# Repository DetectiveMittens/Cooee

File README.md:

# Cooee (A LoRa Phone)                           
An open-source phone that can operate without GSM or LTE coverage. Utilising LoRa modulation and mesh networking to enable long range "off-grid" communication.

Come get involved or just chat here! -> [Discord](https://discord.gg/eWgrdjpTFj)

## Target Utilities/Functions
At time of writing (Jan 2026) Popular LoRa mesh networks only aim to support passing of text messages for public and private chat. Cooee aims to provide more of phone the features that consumers are used to

* __Voice calls:__ using 'Codec2' voice can be heavily compressed into small enough packets as to be supported by ~900MHz LoRa bandwidth limitations. Due to the delay that would happen if these packets needed to be retransmitted, calls would likely only be permitted between devices that have only 1 or 0 repeaters required between them.

* __Navigation:__ Using the data from OpenStreetMaps https://www.openstreetmap.org/ pre-loaded onto the device SD card a GPS reciever and infered location data based on signal strength to fixed repeaters of known location, the Cooee device should be able to locate itself well enough for navigation without ever needing a mobile data connection. 

* __Sending images and files:__
While LoRa bandwidth will likely never support sending large files (videos etc) piecemeal file transfers of compressed images (jpgs) should be possible

## Applications / Uses: 
The Cooee should ideally contribute to solving the following problems
  * Distress calls for help in remote locations
  * Basic communication in areas without GSM/LTE infrastructure
  * Dissemination of natural disaster and emergency warnings
  * Marking/Logging GPS locations. Users could tag and share hazards such as landmines (UXO/ERW), fires, vehicle collisions, chemical spills or dangerous wildlife.
  * Navigation in areas without GSM/LTE infrastructure

## Philosophy: 
My dream for this device is that is could demonstrate my ideals for what the future of harware aught to look like. This means deliberately achieving aims in ways which are not the 'best practice', such as;
 * Keeping code simple, using the Arduino framework isntead of ESP-IDF. The idea being that this increases how many people around the world would be able to understand and modify the device firmware, helping ensure that it is kept on track with providing maximum utility to the lives of those people who own one.
 * No electronic components smaller than 805 (no micro-soldering), this allows people to hand solder in repairs and hand assembly the PCB's with minimal equipement
 * SMT components on one side of the PCB only. Again allowing for easy assembly and repair without specialized gear
 * Plastic parts moulded from post consumer waste. Many plastics today claim to be 'recycled' when really they are just 'factory seconds', they have never used and discarded. I would like the plastic components of the Cooee to be injection moulded from recycld post consumer PET bottled pulled from waterways. Many countries in SEA are flooded with drink bottles made of PET. an easily recycled thermoplastic.
 * Hardware ownership. Increasingly, modern mobile devices are not really the property of the customer who paid hundreds, sometimes thousands of dollars to 'own' it. They are not free to modify it or install custom firmware, even creating custom firmware is a task far beyond the capabilities of most. This leaves people at the mercy of whatever bloatware the manufacturers have bundled. This bundled software often; listens to you at all times, sends transcripts of your conversations to corporate servers, advertises products at you, insists on volunteering additional personal details to enable use ect. I think it's high time that the cleverst people in the world put thier efforts towards creating machines that provide all of the utility that benefits us without any of the data harvesting and advertising. Imagine how nice it would be to use a navigator which simply puts your GPS position on a locally loaded map, it doesn't start suffocating your device by chewing up huge amounts of bandwidth or report everywhere you go to a server or try to encourage spending on nearby businesses. Imagine a navigator which just helps you nagivate in the most lightweight and unobtrusive way possible.
 This is the philisophy I want to see applied to all the functions of the Cooee software.

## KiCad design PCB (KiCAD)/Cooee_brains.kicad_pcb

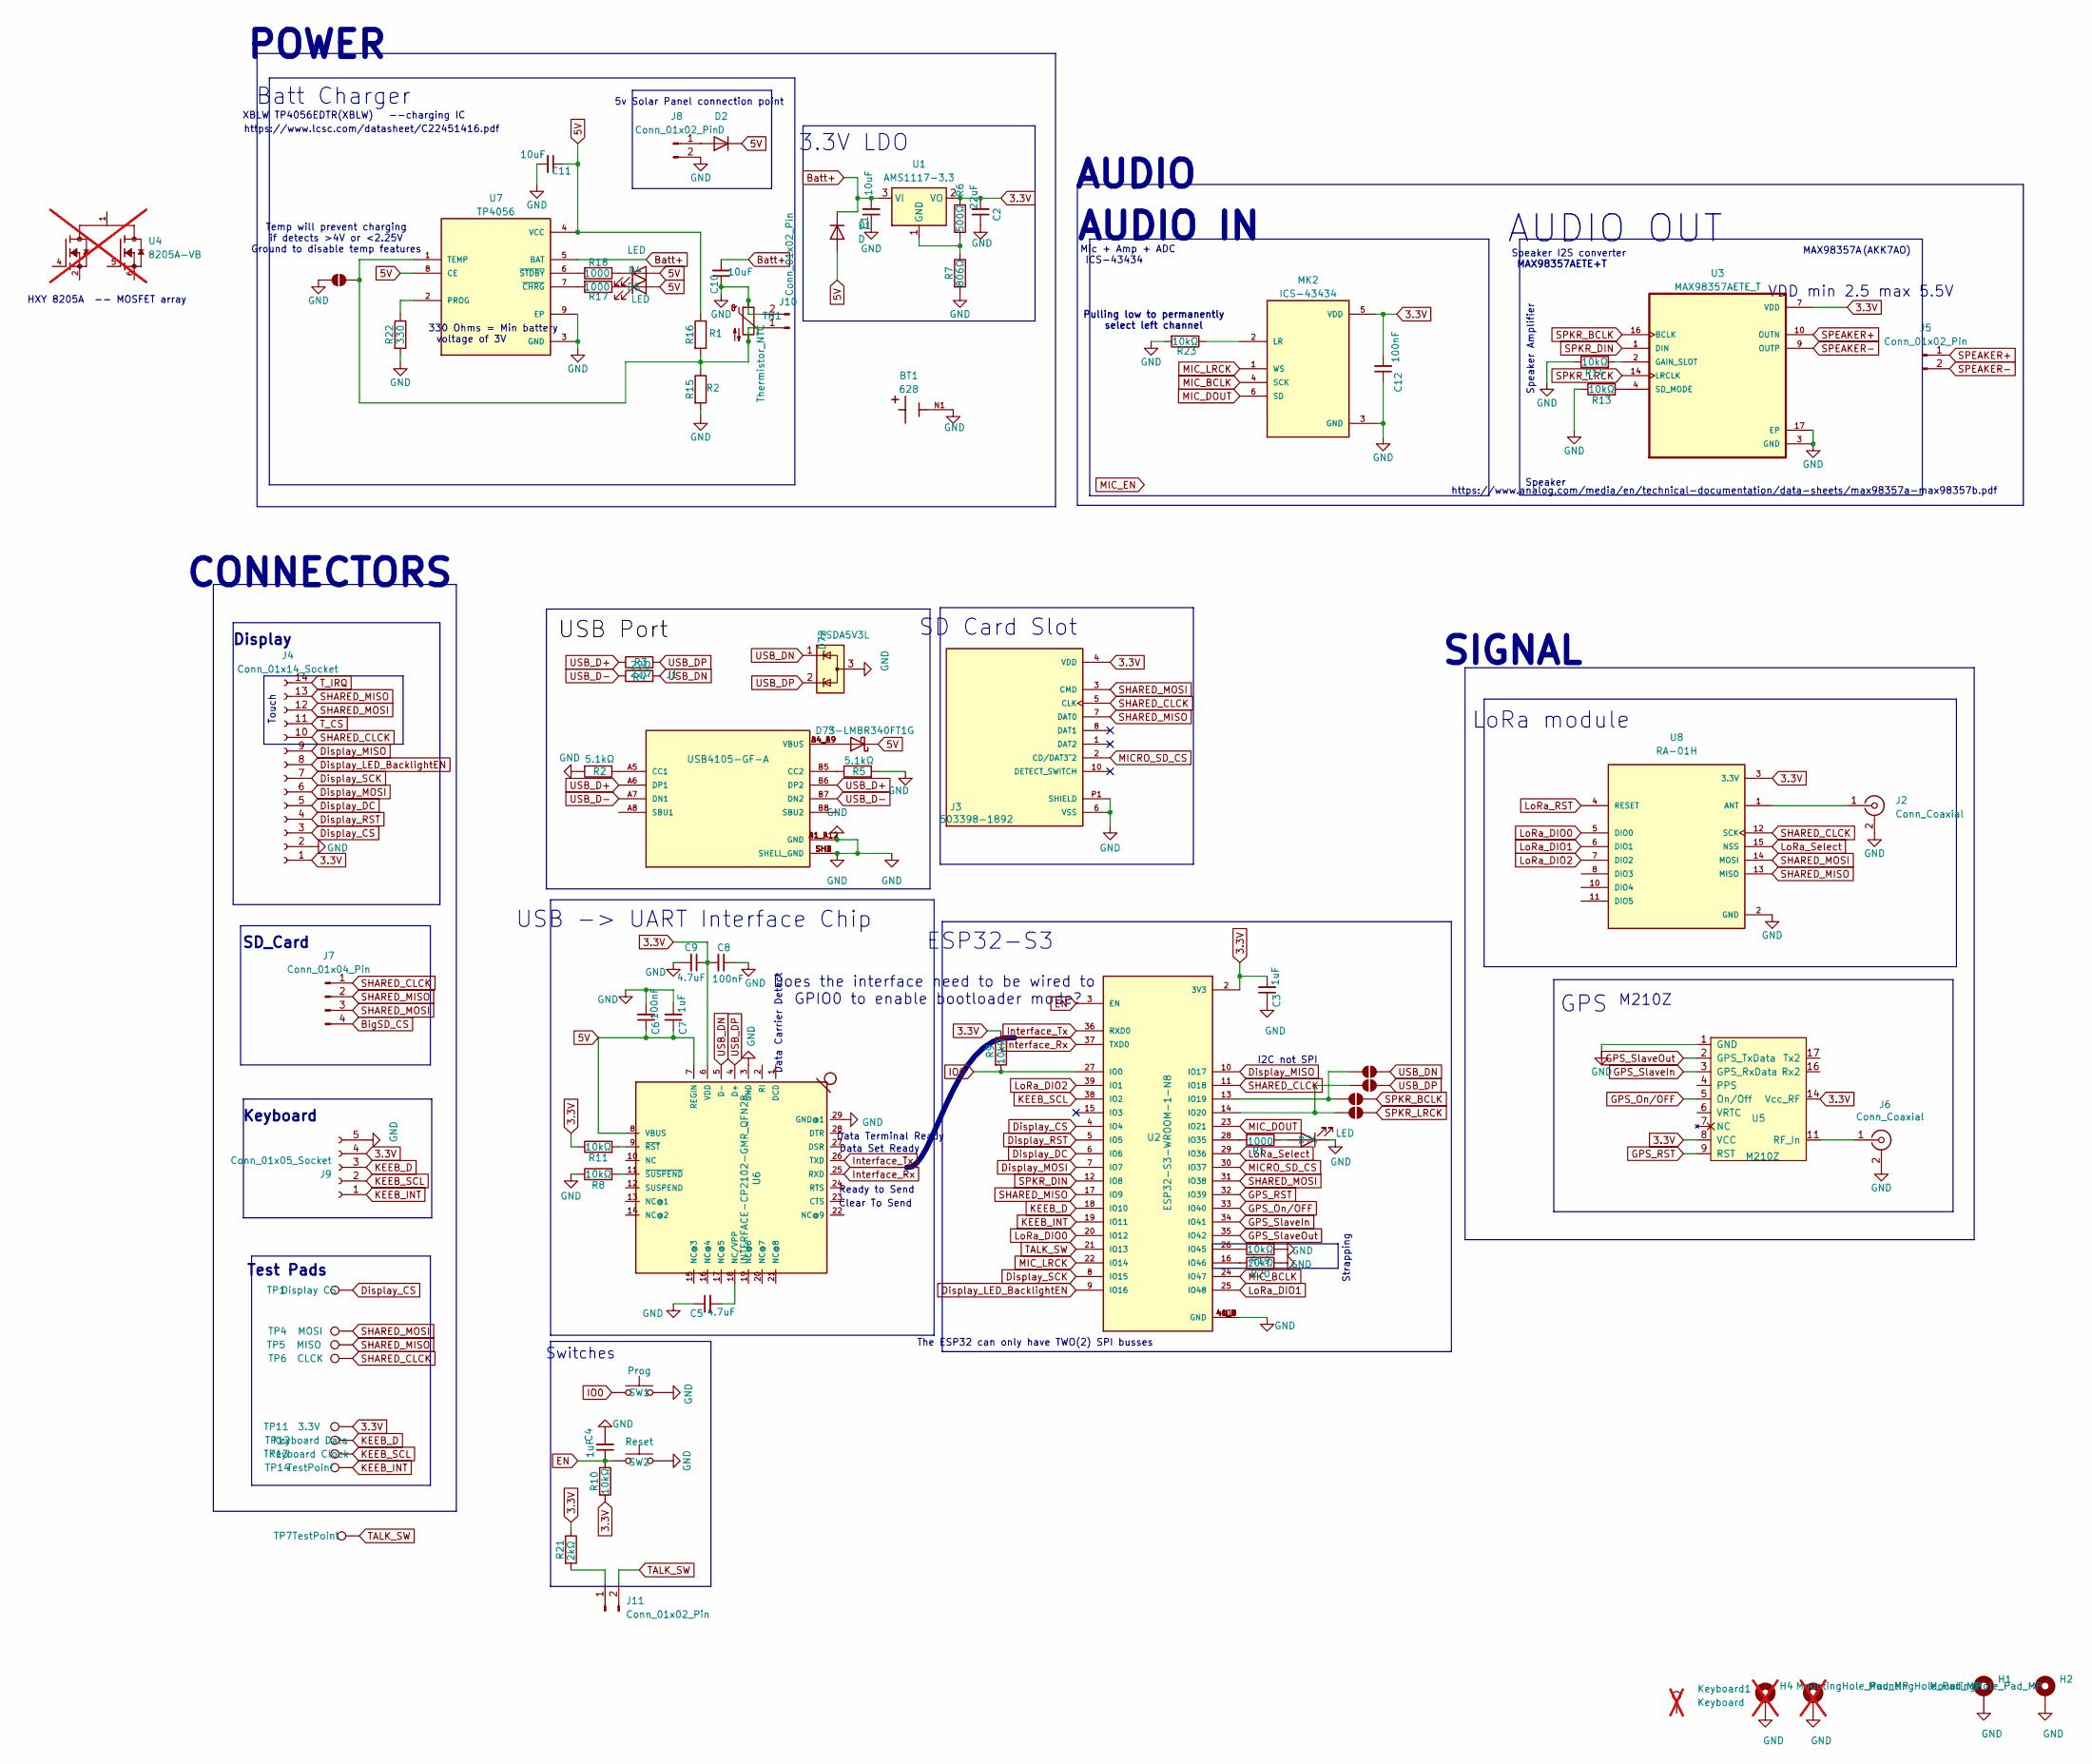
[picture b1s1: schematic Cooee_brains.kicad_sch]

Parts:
BT1: 628; BAT_628; PARTREV A; DigiKey_Part_Number 36-628-ND
C1, C10, C11: 10uF; C_0805_2012Metric
C2: 22uF; C_0805_2012Metric
C3, C7: 1uF; C_0805_2012Metric
C4: 1uF; C_0805_2012Metric_Pad1.18x1.45mm_HandSolder
C5, C9: 4.7uF; C_0805_2012Metric
C6, C8, C12: 100nF; C_0805_2012Metric
D1, D2: D; D_0805_2012Metric_Pad1.15x1.40mm_HandSolder
D4, D5, D74: LED; C_0805_2012Metric
D72: ESDA5V3L; SOT-23_Handsoldering
D73: S-LMBR340FT1G; D_SOD-123FL
H1, H2: MountingHole_Pad_MP; MountingHole_3.2mm_M3_DIN965_Pad_TopBottom
H3, H4: MountingHole_Pad_MP; MountingHole_3.2mm_M3_DIN965_Pad_TopBottom; not fitted
J1: USB4105-GF-A; USB_C_Receptacle_GCT_USB4105-xx-A_16P_TopMnt_Horizontal
J2, J6: Conn_Coaxial; U.FL_Molex_MCRF_73412-0110_Vertical
J3: 503398-1892; MOLEX_503398-1892; PARTREV 0
J4: Conn_01x14_Socket; PinSocket_1x14_P2.54mm_Horizontal
J5, J8, J10, J11: Conn_01x02_Pin; PinHeader_1x02_P2.54mm_Horizontal
J7: Conn_01x04_Pin; PinHeader_1x04_P2.54mm_Horizontal
J9: Conn_01x05_Socket; PinSocket_1x05_P2.54mm_Horizontal
JP1, JP2, JP3, JP4, JP5: SolderJumper_2_Open; SolderJumper-2_P1.3mm_Open_RoundedPad1.0x1.5mm
Keyboard1: Keyboard; TestPoint_Pad_1.0x1.0mm; not fitted
MK2: ICS-43434; MIC_ICS-43434
R1, R17, R18: 1000; C_0805_2012Metric_Pad1.18x1.45mm_HandSolder
R2, R5: 5.1kΩ; R_0805_2012Metric
R3, R4: 22Ω; R_0805_2012Metric
R6: 500Ω; C_0805_2012Metric_Pad1.18x1.45mm_HandSolder
R7: 806Ω; C_0805_2012Metric_Pad1.18x1.45mm_HandSolder
R8, R9, R10, R11, R13, R14, R19, R20, R23: 10kΩ; C_0805_2012Metric_Pad1.18x1.45mm_HandSolder
R15: R2; C_0805_2012Metric_Pad1.18x1.45mm_HandSolder
R16: R1; C_0805_2012Metric_Pad1.18x1.45mm_HandSolder
R21: 2kΩ; C_0805_2012Metric_Pad1.18x1.45mm_HandSolder
R22: 330; C_0805_2012Metric_Pad1.18x1.45mm_HandSolder
SW1: Prog; SW_SPST_B3U-1000P_MovedText
SW2: Reset; SW_SPST_B3U-1000P_MovedText
TH1: Thermistor_NTC; R_0805_2012Metric_Pad1.20x1.40mm_HandSolder
TP1: Display CS; TestPoint_Pad_1.0x1.0mm
TP4: MOSI; TestPoint_Pad_1.0x1.0mm
TP5: MISO; TestPoint_Pad_1.0x1.0mm
TP6: CLCK; TestPoint_Pad_1.0x1.0mm
TP7, TP14: TestPoint; TestPoint_Pad_1.0x1.0mm
TP11: 3.3V; TestPoint_Pad_1.0x1.0mm
TP12: Keyboard Data; TestPoint_Pad_1.0x1.0mm
TP13: Keyboard Clock; TestPoint_Pad_1.0x1.0mm
U1: AMS1117-3.3; SOT-223-3_TabPin2
U2: ESP32-S3-WROOM-1-N8; ESP32-S3-WROOM-1
U3: MAX98357AETE_T; TQFN-16-1EP_3x3mm_P0.5mm_EP1.6x1.6mm
U4: 8205A-VB; SOP65P640X120-8N; PARTREV NA; not fitted
U5: M210Z
U6: INTERFACE-CP2102-GMR_QFN28_; QFN28G_0.5-5X5MM; MPN CP2102-GMR
U7: TP4056; SOP127P600X175-9N
U8: RA-01H; Ai-Thinker-Ra-01-LoRa; PARTREV V1.0; DigiKey_Part_Number 4570-RA-01HCT-ND

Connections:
3.3V: C2.2, C3.2, C8.2, C9.1, C12.2, J3.4 (VDD), J4.1, J9.4, MK2.5 (VDD), R6.2, R9.1, R10.2, R11.1, R21.1, TP11.1, U1.2 (VO), U2.2 (3V3), U3.7 (VDD), U3.8 (VDD), U5.8 (VCC), U5.14 (Vcc_RF), U6.6 (VDD), U8.3 (3.3V)
5V: C6.1, C7.1, C11.1, D1.2 (A), D2.1 (K), D4.2 (A), D5.2 (A), D73.1 (K), R16.1, U6.7 (REGIN), U6.8 (VBUS), U7.4 (VCC), U7.8 (CE)
Batt+: C1.2, C10.2, D1.1 (K), U1.3 (VI), U7.5 (BAT)
BigSD_CS: J7.4
Display_CS: J4.3, TP1.1, U2.4 (IO4)
Display_DC: J4.5, U2.6 (IO6)
Display_LED_BacklightEN: J4.8, U2.9 (IO16)
Display_MISO: J4.9, U2.10 (IO17)
Display_MOSI: J4.6, U2.7 (IO7)
Display_RST: J4.4, U2.5 (IO5)
Display_SCK: J4.7, U2.8 (IO15)
EN: C4.1, R10.1, SW2.1, U2.3 (EN)
GND: BT1.N1, BT1.N2, BT1.N3, C1.1, C2.1, C3.1, C4.2, C5.1, C6.2, C7.2, C8.1, C9.2, C10.1, C11.2, C12.1, D72.3 (A), D74.1 (K), H1.1, H1.MP, H2.1, H2.MP, H3.MP, H4.MP, J1.A1_B12 (GND), J1.B1_A12 (GND), J1.S1, J1.SH1 (SHELL_GND), J1.SH2 (SHELL_GND), J1.SH3 (SHELL_GND), J1.SH4 (SHELL_GND), J2.2 (Ext), J3.6 (VSS), J3.9 (VSS), J3.P1 (SHIELD), J3.P2 (SHIELD), J3.P3 (SHIELD), J3.P4 (SHIELD), J4.2, J6.2 (Ext), J8.2, J9.5, J10.2, JP5.1 (A), MK2.3 (GND), R2.2, R5.2, R7.2, R8.1, R13.1, R14.1, R15.2, R19.2, R20.2, R22.2, R23.2, SW1.2, SW2.2, TH1.1, U2.1 (GND), U2.40 (GND), U2.41, U2.41_1 (GND), U2.41_2 (GND), U2.41_3 (GND), U2.41_4 (GND), U2.41_5 (GND), U2.41_6 (GND), U2.41_7 (GND), U2.41_8 (GND), U2.41_9 (GND), U2.GND, U3.3 (GND), U3.11 (GND), U3.15 (GND), U3.17 (EP), U5.1 (GND), U6.3 (GND), U6.29 (GND@1), U7.3 (GND), U7.9 (EP), U8.2 (GND), U8.9 (GND), U8.16 (GND)
GPS_On/OFF: U2.33 (IO40), U5.5 (On/Off)
GPS_RST: U2.32 (IO39), U5.9 (RST)
GPS_SlaveIn: U2.34 (IO41), U5.3 (GPS_RxData)
GPS_SlaveOut: U2.35 (IO42), U5.2 (GPS_TxData)
IO0: R9.2, SW1.1, U2.27 (IO0)
Interface_Rx: U2.37 (TXD0), U6.25 (RXD)
Interface_Tx: U2.36 (RXD0), U6.26 (TXD)
KEEB_D: J9.3, TP12.1, U2.18 (IO10)
KEEB_INT: J9.1, TP14.1, U2.19 (IO11)
KEEB_SCL: J9.2, TP13.1, U2.38 (IO2)
LoRa_DIO0: U2.20 (IO12), U8.5 (DIO0)
LoRa_DIO1: U2.25 (IO48), U8.6 (DIO1)
LoRa_DIO2: U2.39 (IO1), U8.7 (DIO2)
LoRa_RST: U8.4 (RESET)
LoRa_Select: U2.29 (IO36), U8.15 (NSS)
MICRO_SD_CS: J3.2 (CD/DAT3^2), U2.30 (IO37)
MIC_BCLK: MK2.4 (SCK), U2.24 (IO47)
MIC_DOUT: MK2.6 (SD), U2.23 (IO21)
MIC_LRCK: MK2.1 (WS), U2.22 (IO14)
unnamed: D2.2 (A), J8.1
unnamed: D4.1 (K), R18.1
unnamed: D5.1 (K), R17.1
unnamed: D73.2 (A), J1.A4_B9 (VBUS), J1.B4_A9 (VBUS)
unnamed: D74.2 (A), R1.1
unnamed: J1.A5 (CC1), R2.1
unnamed: J1.B5 (CC2), R5.1
unnamed: J2.1 (In), U8.1 (ANT)
unnamed: J6.1 (In), U5.11 (RF_In)
unnamed: J10.1, JP5.2 (B), R15.1, R16.2, TH1.2, U7.1 (TEMP)
unnamed: J11.1, R21.2
unnamed: JP1.1 (A), JP3.1 (A), U2.13 (IO19)
unnamed: JP2.1 (A), JP4.1 (A), U2.14 (IO20)
unnamed: MK2.2 (LR), R23.1
unnamed: R6.1, R7.1, U1.1 (GND)
unnamed: R1.2, U2.28 (IO35)
unnamed: R19.1, U2.26 (IO45)
unnamed: R20.1, U2.16 (IO46)
unnamed: R14.2, U3.2 (GAIN_SLOT)
unnamed: R13.2, U3.4 (SD_MODE)
unnamed: U4.1, U4.8
unnamed: U4.2, U4.3
unnamed: U4.6, U4.7
unnamed: C5.2, U6.18 (NC/VPP)
unnamed: R11.2, U6.9 (~RST)
unnamed: R8.2, U6.11 (~SUSPEND)
unnamed: R22.1, U7.2 (PROG)
unnamed: R17.2, U7.7 (~CHRG)
unnamed: R18.2, U7.6 (~STDBY)
SHARED_CLCK: J3.5 (CLK), J4.10, J7.1, TP6.1, U2.11 (IO18), U8.12 (SCK)
SHARED_MISO: J3.7 (DAT0), J4.13, J7.2, TP5.1, U2.17 (IO9), U8.13 (MISO)
SHARED_MOSI: J3.3 (CMD), J4.12, J7.3, TP4.1, U2.31 (IO38), U8.14 (MOSI)
SPEAKER+: J5.1, U3.10 (OUTN)
SPEAKER-: J5.2, U3.9 (OUTP)
SPKR_BCLK: JP3.2 (B), U3.16 (BCLK)
SPKR_DIN: U2.12 (IO8), U3.1 (DIN)
SPKR_LRCK: JP4.2 (B), U3.14 (LRCLK)
TALK_SW: J11.2, TP7.1, U2.21 (IO13)
T_CS: J4.11
T_IRQ: J4.14
USB_D+: J1.A6 (DP1), J1.B6 (DP2), R3.1
USB_D-: J1.A7 (DN1), J1.B7 (DN2), R4.1
USB_DN: D72.1 (K), JP1.2 (B), R4.2, U6.5 (D-)
USB_DP: D72.2 (K), JP2.2 (B), R3.2, U6.4 (D+)

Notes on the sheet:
SIGNAL
Does the interface need to be wired to GPIO0 to enable bootloader mode?
Data Set Ready
MAX98357AETE+T
Data Carrier Detect
AUDIO
The ESP32 can only have TWO(2) SPI busses
https://www.analog.com/media/en/technical-documentation/data-sheets/max98357a-max98357b.pdf
POWER
Speaker Amplifier
M210Z
https://www.lcsc.com/datasheet/C22451416.pdf
voltage of 3V
XBLW TP4056EDTR(XBLW) --charging IC
Strapping
AUDIO IN
Speaker I2S converter
ESP32-S3
Switches
ICS-43434
HXY 8205A -- MOSFET array
SD Card Slot
Ready to Send
Speaker
VDD min 2.5 max 5.5V
Clear To Send
I2C not SPI
SD_Card
5v Solar Panel connection point
AUDIO OUT
Batt Charger
CONNECTORS
Temp will prevent charging if detects >4V or <2.25V Ground to disable temp features
Pulling low to permanently select left channel
USB -> UART Interface Chip
Keyboard
3.3V LDO
Touch
GPS
Test Pads

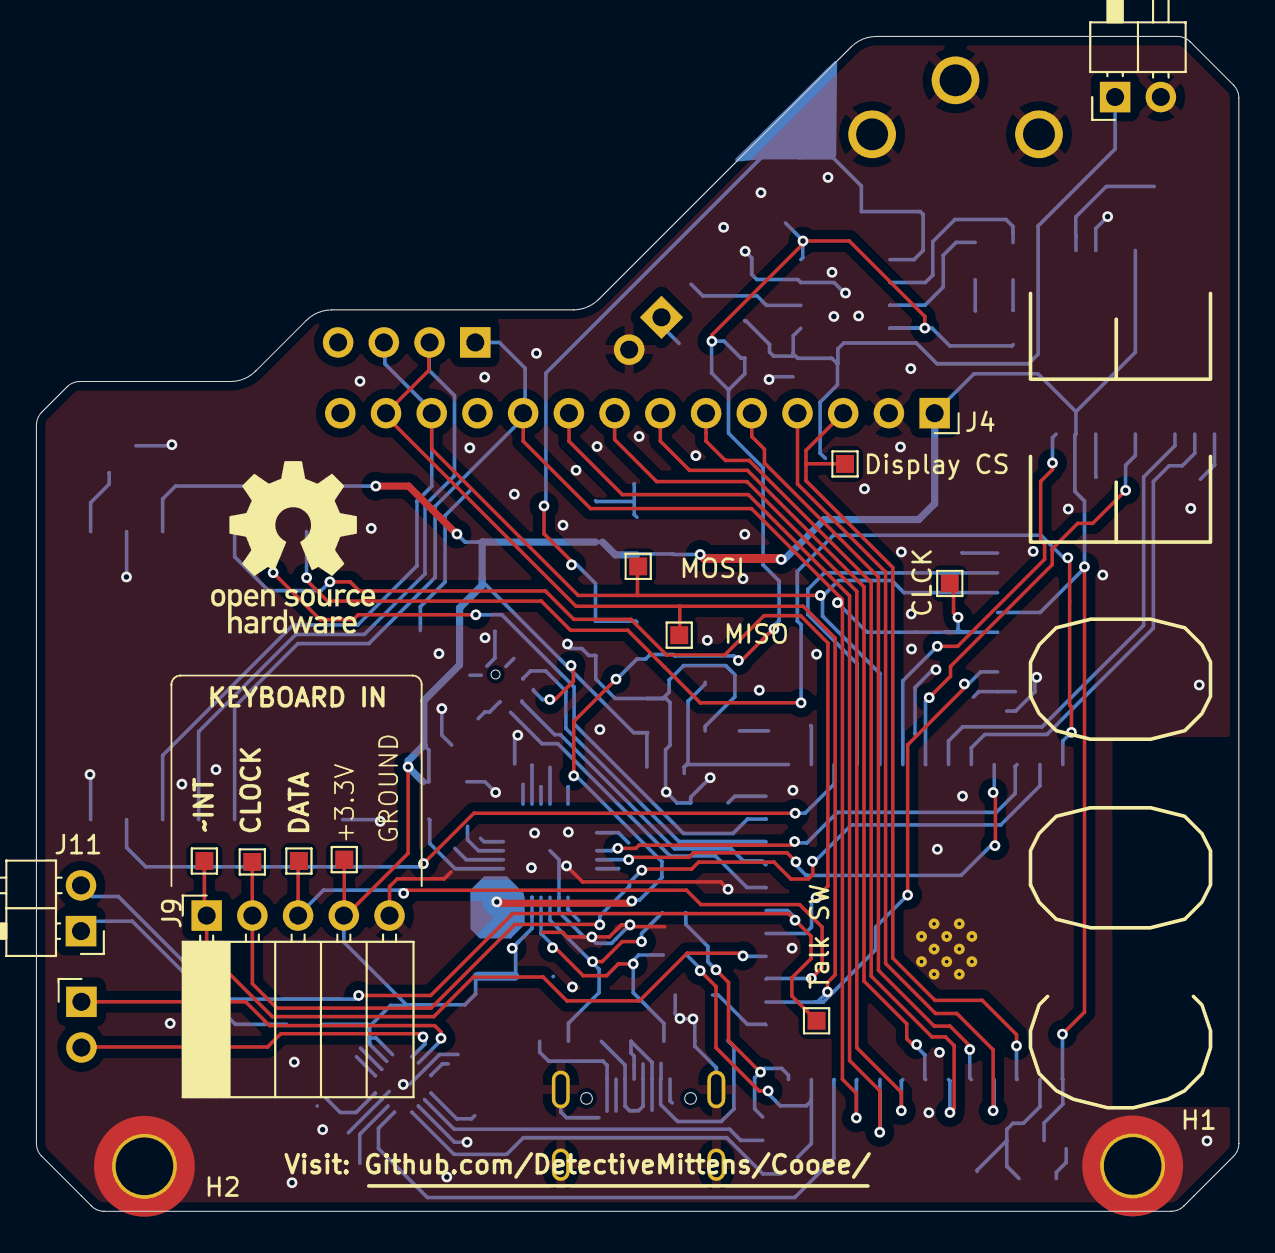
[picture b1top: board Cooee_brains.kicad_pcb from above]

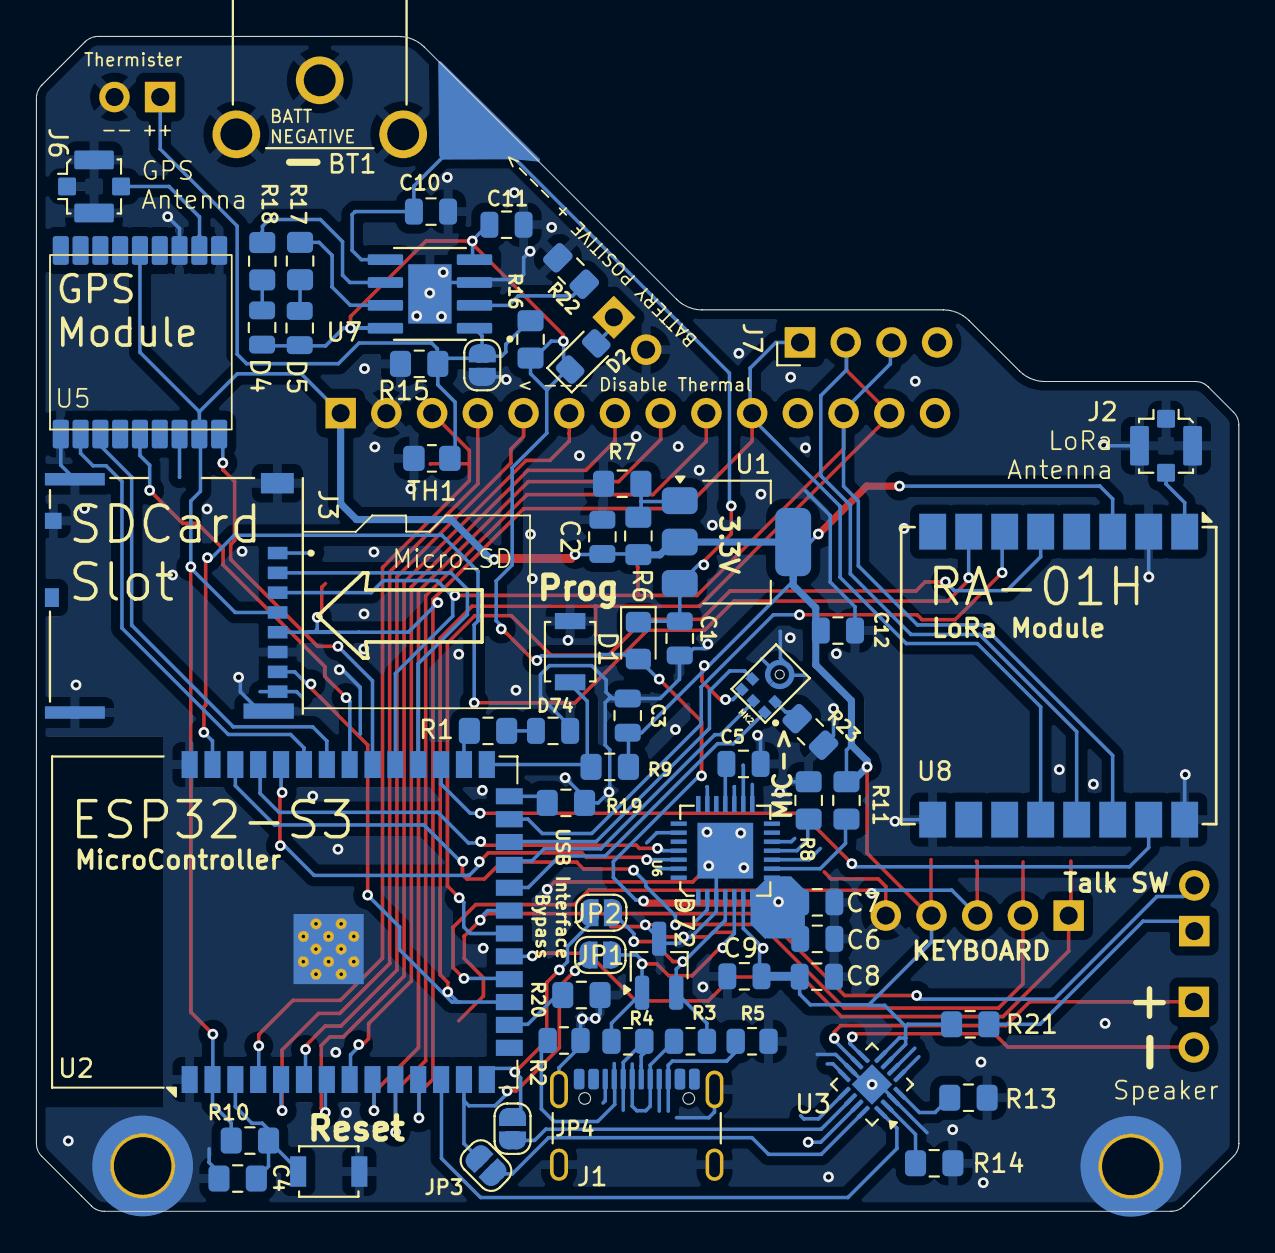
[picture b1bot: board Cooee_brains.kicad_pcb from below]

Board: 2 copper layers, 66.8 x 65.3 mm, 79 parts (63 on the bottom side), 68 nets.

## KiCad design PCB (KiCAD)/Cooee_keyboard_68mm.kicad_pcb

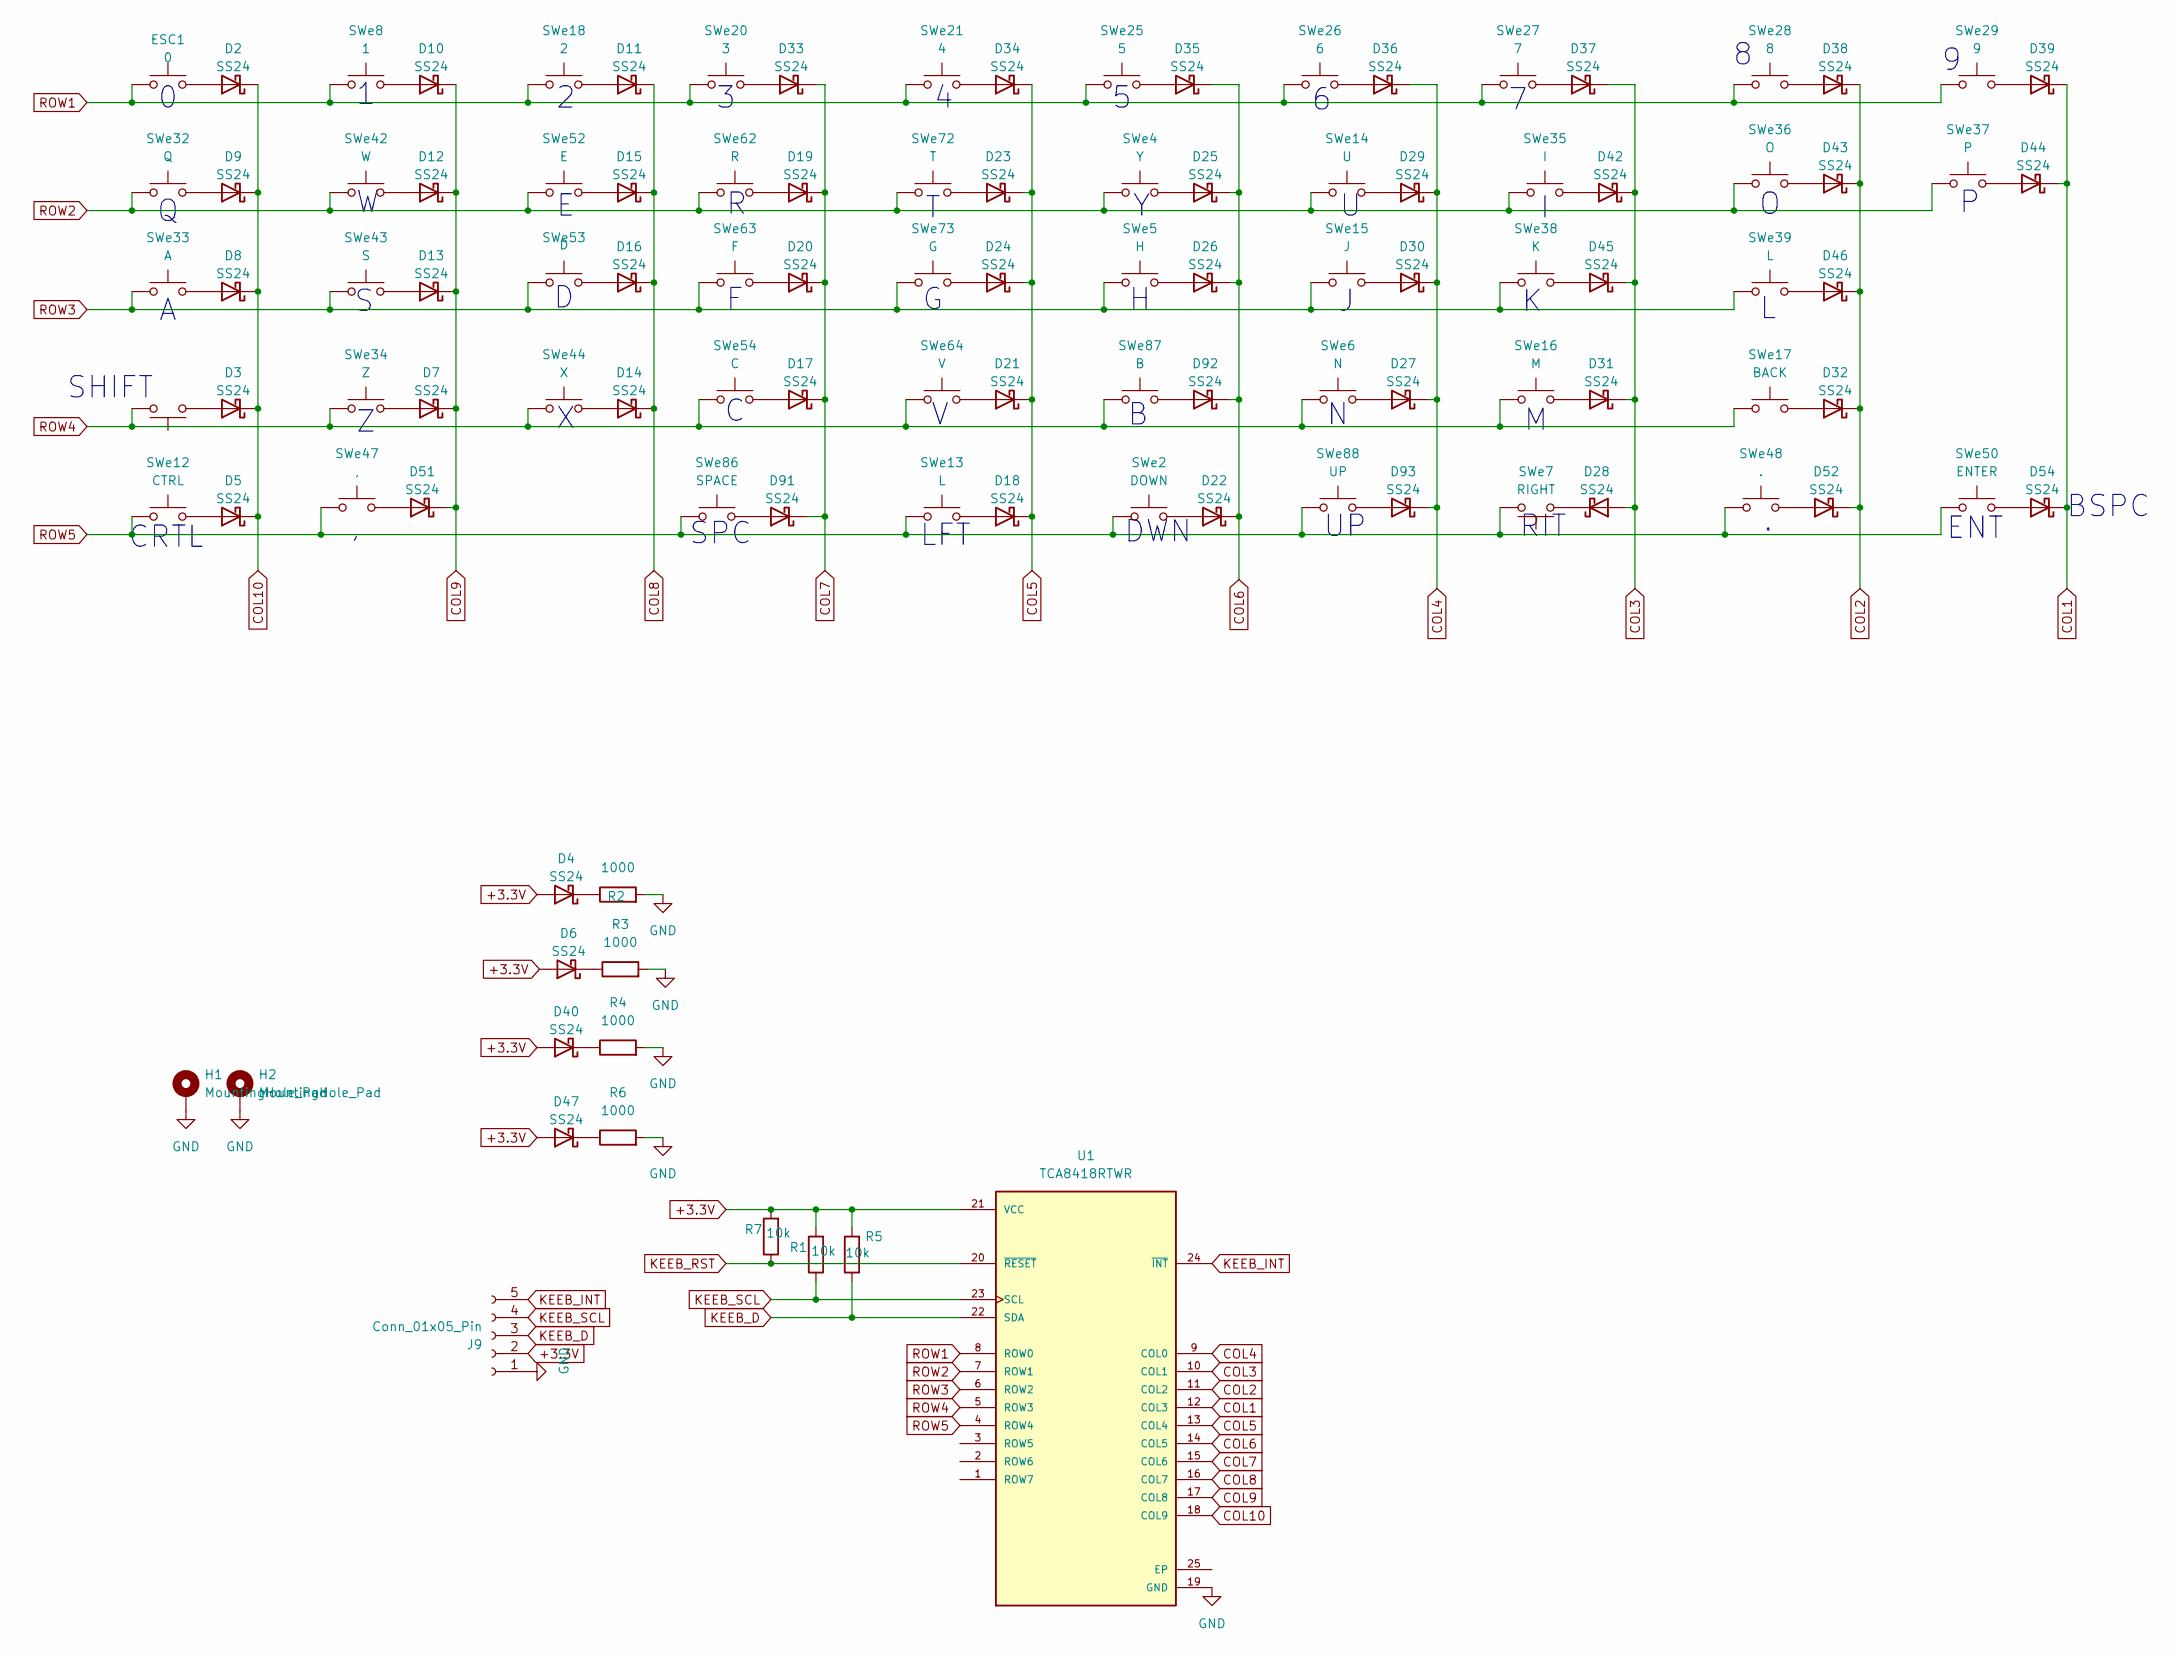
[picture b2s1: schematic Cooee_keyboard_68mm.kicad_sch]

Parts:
D2, D3, D4, D5, D6, D7, D8, D9, D10, D11, D12, D13, D14, D15, D16, D17, D18, D19, D20, D21, D22, D23, D24, D25, D26, D27, D28, D29, D30, D31, D32, D33, D34, D35, D36, D37, D38, D39, D40, D42, D43, D44, D45, D46, D47, D51, D52, D54, D91, D92, D93: SS24; D_0805_2012Metric
ESC1: 0; SW_SPST_B3U-1000P_MovedText
H1, H2: MountingHole_Pad; MountingHole_3.2mm_M3_DIN965_Pad_TopBottom
J9: Conn_01x05_Pin; PinHeader_1x05_P2.54mm_Horizontal
R1, R5, R7: 10k; R_0805_2012Metric_Pad1.20x1.40mm_HandSolder
R2, R3, R4, R6: 1000; R_0805_2012Metric_Pad1.20x1.40mm_HandSolder
SWe2: DOWN; SW_SPST_B3U-1000P_MovedText
SWe4: Y; SW_SPST_B3U-1000P_MovedText
SWe5: H; SW_SPST_B3U-1000P_MovedText
SWe6: N; SW_SPST_B3U-1000P_MovedText
SWe7: RIGHT; SW_SPST_B3U-1000P_MovedText
SWe8: 1; SW_SPST_B3U-1000P_MovedText
SWe12: CTRL; SW_SPST_B3U-1000P_MovedText
SWe13, SWe39: L; SW_SPST_B3U-1000P_MovedText
SWe14: U; SW_SPST_B3U-1000P_MovedText
SWe15: J; SW_SPST_B3U-1000P_MovedText
SWe16: M; SW_SPST_B3U-1000P_MovedText
SWe17: BACK; SW_SPST_B3U-1000P_MovedText
SWe18: 2; SW_SPST_B3U-1000P_MovedText
SWe20: 3; SW_SPST_B3U-1000P_MovedText
SWe21: 4; SW_SPST_B3U-1000P_MovedText
SWe24: SFT; SW_SPST_B3U-1000P_MovedText
SWe25: 5; SW_SPST_B3U-1000P_MovedText
SWe26: 6; SW_SPST_B3U-1000P_MovedText
SWe27: 7; SW_SPST_B3U-1000P_MovedText
SWe28: 8; SW_SPST_B3U-1000P_MovedText
SWe29: 9; SW_SPST_B3U-1000P_MovedText
SWe32: Q; SW_SPST_B3U-1000P_MovedText
SWe33: A; SW_SPST_B3U-1000P_MovedText
SWe34: Z; SW_SPST_B3U-1000P_MovedText
SWe35: I; SW_SPST_B3U-1000P_MovedText
SWe36: O; SW_SPST_B3U-1000P_MovedText
SWe37: P; SW_SPST_B3U-1000P_MovedText
SWe38: K; SW_SPST_B3U-1000P_MovedText
SWe42: W; SW_SPST_B3U-1000P_MovedText
SWe43: S; SW_SPST_B3U-1000P_MovedText
SWe44: X; SW_SPST_B3U-1000P_MovedText
SWe47: ,; SW_SPST_B3U-1000P_MovedText
SWe48: .; SW_SPST_B3U-1000P_MovedText
SWe50: ENTER; SW_SPST_B3U-1000P_MovedText
SWe52: E; SW_SPST_B3U-1000P_MovedText
SWe53: D; SW_SPST_B3U-1000P_MovedText
SWe54: C; SW_SPST_B3U-1000P_MovedText
SWe62: R; SW_SPST_B3U-1000P_MovedText
SWe63: F; SW_SPST_B3U-1000P_MovedText
SWe64: V; SW_SPST_B3U-1000P_MovedText
SWe72: T; SW_SPST_B3U-1000P_MovedText
SWe73: G; SW_SPST_B3U-1000P_MovedText
SWe86: SPACE; SW_SPST_B3U-1000P_MovedText
SWe87: B; SW_SPST_B3U-1000P_MovedText
SWe88: UP; SW_SPST_B3U-1000P_MovedText
U1: TCA8418RTWR; QFN50P400X400X100-25N; PARTREV G

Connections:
+3.3V: D4.2 (A), D6.2 (A), D40.2 (A), D47.2 (A), J9.2, R1.2, R5.2, R7.2, U1.21 (VCC)
COL1: D39.1 (K), D44.1 (K), D54.1 (K), U1.12 (COL3)
COL2: D32.1 (K), D38.1 (K), D43.1 (K), D46.1 (K), D52.1 (K), U1.11 (COL2)
COL3: D28.2 (A), D31.1 (K), D37.1 (K), D42.1 (K), D45.1 (K), U1.10 (COL1)
COL4: D27.1 (K), D29.1 (K), D30.1 (K), D36.1 (K), D93.1 (K), U1.9 (COL0)
COL5: D18.1 (K), D21.1 (K), D23.1 (K), D24.1 (K), D34.1 (K), U1.13 (COL4)
COL6: D22.1 (K), D25.1 (K), D26.1 (K), D35.1 (K), D92.1 (K), U1.14 (COL5)
COL7: D17.1 (K), D19.1 (K), D20.1 (K), D33.1 (K), D91.1 (K), U1.15 (COL6)
COL8: D11.1 (K), D14.1 (K), D15.1 (K), D16.1 (K), U1.16 (COL7)
COL9: D7.1 (K), D10.1 (K), D12.1 (K), D13.1 (K), D51.1 (K), U1.17 (COL8)
COL10: D2.1 (K), D3.1 (K), D5.1 (K), D8.1 (K), D9.1 (K), U1.18 (COL9)
GND: H1.1, H2.1, J9.1, R2.2, R3.2, R4.2, R6.2, U1.19 (GND)
KEEB_D: J9.3, R5.1, U1.22 (SDA)
KEEB_INT: J9.5, U1.24 (~INT)
KEEB_RST: R7.1, U1.20 (~RESET)
KEEB_SCL: J9.4, R1.1, U1.23 (SCL)
unnamed: D2.2 (A), ESC1.2
unnamed: D3.2 (A), SWe24.2
unnamed: D4.1 (K), R2.1
unnamed: D5.2 (A), SWe12.2
unnamed: D6.1 (K), R3.1
unnamed: D7.2 (A), SWe34.2
unnamed: D8.2 (A), SWe33.2
unnamed: D9.2 (A), SWe32.2
unnamed: D10.2 (A), SWe8.2
unnamed: D11.2 (A), SWe18.2
unnamed: D12.2 (A), SWe42.2
unnamed: D13.2 (A), SWe43.2
unnamed: D14.2 (A), SWe44.2
unnamed: D15.2 (A), SWe52.2
unnamed: D16.2 (A), SWe53.2
unnamed: D17.2 (A), SWe54.2
unnamed: D18.2 (A), SWe13.2
unnamed: D19.2 (A), SWe62.2
unnamed: D20.2 (A), SWe63.2
unnamed: D21.2 (A), SWe64.2
unnamed: D22.2 (A), SWe2.2
unnamed: D23.2 (A), SWe72.2
unnamed: D24.2 (A), SWe73.2
unnamed: D25.2 (A), SWe4.2
unnamed: D26.2 (A), SWe5.2
unnamed: D27.2 (A), SWe6.2
unnamed: D28.1 (K), SWe7.1
unnamed: D29.2 (A), SWe14.2
unnamed: D30.2 (A), SWe15.2
unnamed: D31.2 (A), SWe16.2
unnamed: D32.2 (A), SWe17.2
unnamed: D33.2 (A), SWe20.2
unnamed: D34.2 (A), SWe21.2
unnamed: D35.2 (A), SWe25.2
unnamed: D36.2 (A), SWe26.2
unnamed: D37.2 (A), SWe27.2
unnamed: D38.2 (A), SWe28.2
unnamed: D39.2 (A), SWe29.2
unnamed: D40.1 (K), R4.1
unnamed: D42.2 (A), SWe35.2
unnamed: D43.2 (A), SWe36.2
unnamed: D44.2 (A), SWe37.2
unnamed: D45.2 (A), SWe38.2
unnamed: D46.2 (A), SWe39.2
unnamed: D47.1 (K), R6.1
unnamed: D51.2 (A), SWe47.2
unnamed: D52.2 (A), SWe48.2
unnamed: D54.2 (A), SWe50.2
unnamed: D91.2 (A), SWe86.2
unnamed: D92.2 (A), SWe87.2
unnamed: D93.2 (A), SWe88.2
ROW1: ESC1.1, SWe8.1, SWe18.1, SWe20.1, SWe21.1, SWe25.1, SWe26.1, SWe27.1, SWe28.1, SWe29.1, U1.8 (ROW0)
ROW2: SWe4.1, SWe14.1, SWe32.1, SWe35.1, SWe36.1, SWe37.1, SWe42.1, SWe52.1, SWe62.1, SWe72.1, U1.7 (ROW1)
ROW3: SWe5.1, SWe15.1, SWe33.1, SWe38.1, SWe39.1, SWe43.1, SWe53.1, SWe63.1, SWe73.1, U1.6 (ROW2)
ROW4: SWe6.1, SWe16.1, SWe17.1, SWe24.1, SWe34.1, SWe44.1, SWe54.1, SWe64.1, SWe87.1, U1.5 (ROW3)
ROW5: SWe2.1, SWe7.2, SWe12.1, SWe13.1, SWe47.1, SWe48.1, SWe50.1, SWe86.1, SWe88.1, U1.4 (ROW4)

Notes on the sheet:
ENT
CRTL
LFT
SHIFT
DWN
SPC
RIT
BSPC

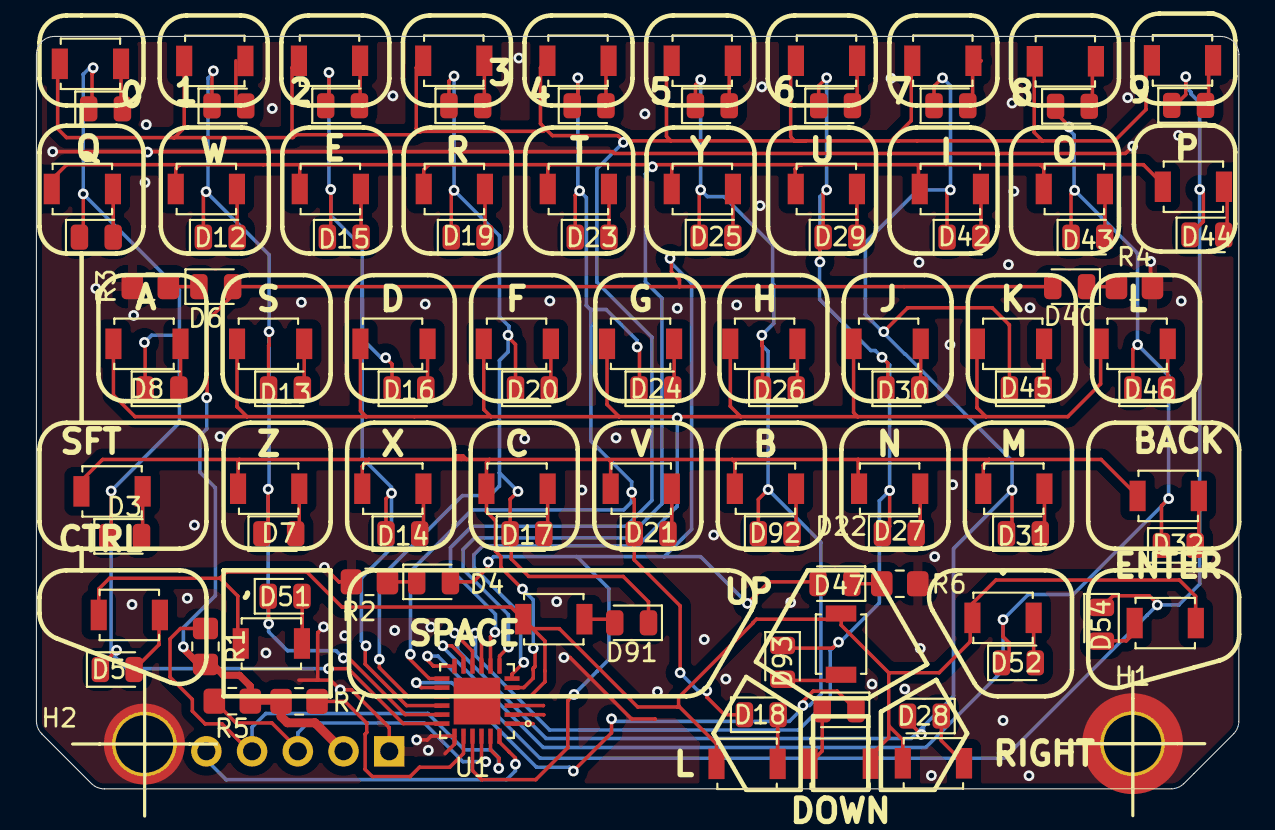
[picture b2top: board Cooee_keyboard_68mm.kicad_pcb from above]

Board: 2 copper layers, 66.8 x 41.8 mm, 109 parts (1 on the bottom side), 72 nets.

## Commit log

2026-01-09 initial commit of PCB project
    initial commit of PCB project
2026-01-10 split PCB into 2 PCB's
    now has multiple PCB's one for computer and one for the keyboard
2026-01-10 changed computer PCB edge shape to match keyboard
    So these can be 2x 2layer boards back to back, easy PnP/hotplate assembly, more modular (replaceable keyboards)
2026-01-10 initial commit of CAD assembly
    initial commit of CAD assembly
2026-01-15 more
    i write enough of these for work
2026-01-16 finished routing new smaller keyboard
    finished routing new smaller keyboard
2026-01-17 finished keyboard at 67mm
    started work on esp32 motherboard
2026-01-19 motherboard PCB layout work
    motherboard PCB layout work
2026-01-24 Updated README.md
    Updated README.md
2026-01-24 swapped out complex SX1262 circuitry for a module
    swapped out complex SX1262 circuitry for a module
2026-01-24 removed kiCad auto-backups from tracked files
    yeah
2026-01-26 cleaned up the silkscreen for keyboard PCB
    cleaned up the silkscreen for keyboard PCB, ordered prototypes
2026-02-02 more PCB work
    should have the 90 degree SMD header pins lined up to mount now, unfortunately I've invalidated the keyboard prototypes I already bought
2026-02-07 new IC choices for GPS, audio and power
    also added a keyboard IC to the keyboard to preventing wasting precious ESP32 GPIOs
2026-02-14 adding some of my coding work
    currently I'm just trying to get audio tranferred over LoRa using two heltecv3.2 boards. All I have so far is reading the microphone in
2026-02-19 finalized next prototype of keyboard PCB, ready to order
    finalized next prototype of keyboard PCB, ready to order
2026-02-19 adding pio config and gitignore
    adding pio config and gitignore
2026-02-20 pcb layout work on phone motherboard
    pcb layout work on phone motherboard
2026-02-21 more PCB work on the motherboard
    more PCB work on the motherboard
2026-02-23 motherboard PCB work
    motherboard PCB work
2026-02-28 trying to figure out the dang i2s device configurations
    trying to figure out the dang i2s device configurations
2026-03-04 got the i2s configurations right to be able to read and write audio!
    hooray!
2026-03-04 progress on audio testing code
    progress on audio testing code
2026-03-05 attempting to compress audio
    attempting to compress audio
2026-03-05 hacked the device sample rates
    half the microphone samples are not discarded due to it's minimum sample rate of 16kHz
2026-03-05 work work
    work work
2026-03-07 centred the USB port and screen properly
    centred the USB port and screen properly. trying to implement compressed audio over radio but compression function started throwing stack overflow
2026-03-11 got past the stack overflow when encoding audio samples
    got past the stack overflow when encoding audio samples
2026-03-12 pcb work
    pcb work
2026-03-13 fixed up some incorrect footprints/symbols
    fixed up some incorrect footprints/symbols
2026-03-14 Expanded README with philosophy section
    Added a philosophy section outlining the design principles and ideals for the Cooee device, focusing on simplicity, repairability, and hardware ownership.
2026-03-14 debugging the encoding and sending of voice data
    debugging the encoding and sending of voice data
2026-03-17 solidworks parts experimenteing, latest code
    solidworks parts experimenteing, latest code
